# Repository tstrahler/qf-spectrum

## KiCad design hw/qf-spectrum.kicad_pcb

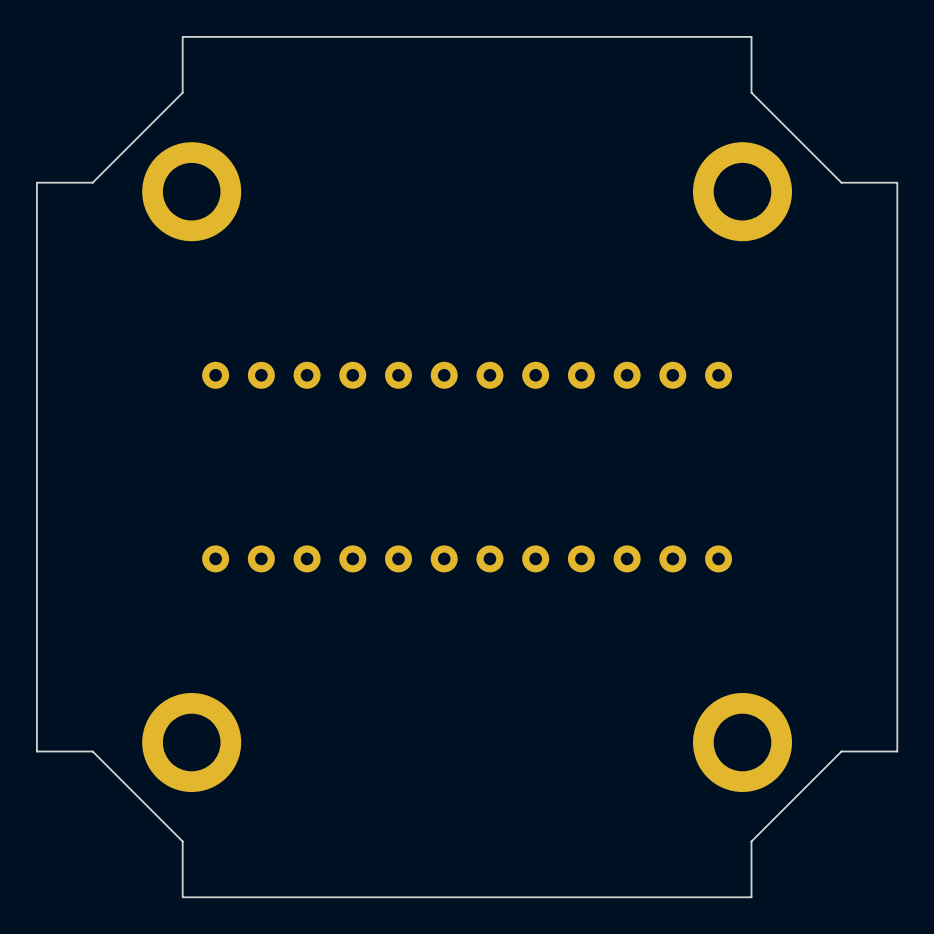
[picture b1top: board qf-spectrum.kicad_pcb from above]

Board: 2 copper layers, 47.8 x 47.8 mm, 5 parts (1 on the bottom side), 2 nets, no tracks yet.

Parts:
H1, H2, H3, H4: MountingHole; MountingHole_3.2mm_M3_ISO14580_Pad
U2: IC_S10077

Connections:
+3V3: U2.8 (Vdd), U2.19 (Vsel), U2.21 (Vdd)
GND: U2.9 (Vss), U2.20 (Vss)
